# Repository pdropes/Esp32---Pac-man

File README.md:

# Esp32_ST7789_Pacman
 Remake of the famous pac-man, with some improvements

!!! NOTICE !!!

## Prepare
- This board was designed to be possible to do at home; the battery is the BL-5B or BL-5C, and the speaker is 32ohms from the 3310.
- In difficulty to find all components, the layout must be changed to support different ones.

## Development Environment
- [Arduino IDE](https://www.arduino.cc/en/main/software)
- [arduino-esp32](https://github.com/espressif/arduino-esp32)

1º Connect the board via USB to the PC.

2º The top buttons are for programming, on the left, IO0, on the right, RESET micro.
For the microcontroller to enter programming mode, the IO0 button must be held down while pressing the reset button briefly.

3º In the Arduino environment, choose "ESP32S2 Dev Module" board.

4º Upload, done.

## Controller
All commands are made on board by switches
LEFT-RIGHT-UP-DOWN , BUTTON A for new game, BUTTON B for pause

## Coding reference
- [Pacman-Arduino-Due](https://github.com/DrNCXCortex/Pacman-Arduino-Due)
- [esp32_ILI9328_Pacman](https://github.com/MhageGH/esp32_ILI9328_Pacman)

Changes:

- Schematic and connections for prototype
- ST7789 support
- Sounds trought two ESP32 8b DAC channels (ambient / effects)
- Functions of buttons A and B
- Show frightened ghosts blinking, before changing to normal
- Battery capacity monitor
- Hiscore saved in internal flash
- Slide-switch to select mode "off/charge" "on/mute" "on/sound"

Revision 1:
- "Battery" font, identical to the rest of the text
- In DEMO mode, the score always remains visible from the last game
- Added missing "Adafruit_BusIO" library

It was my first time programming in C, it may not be perfect.

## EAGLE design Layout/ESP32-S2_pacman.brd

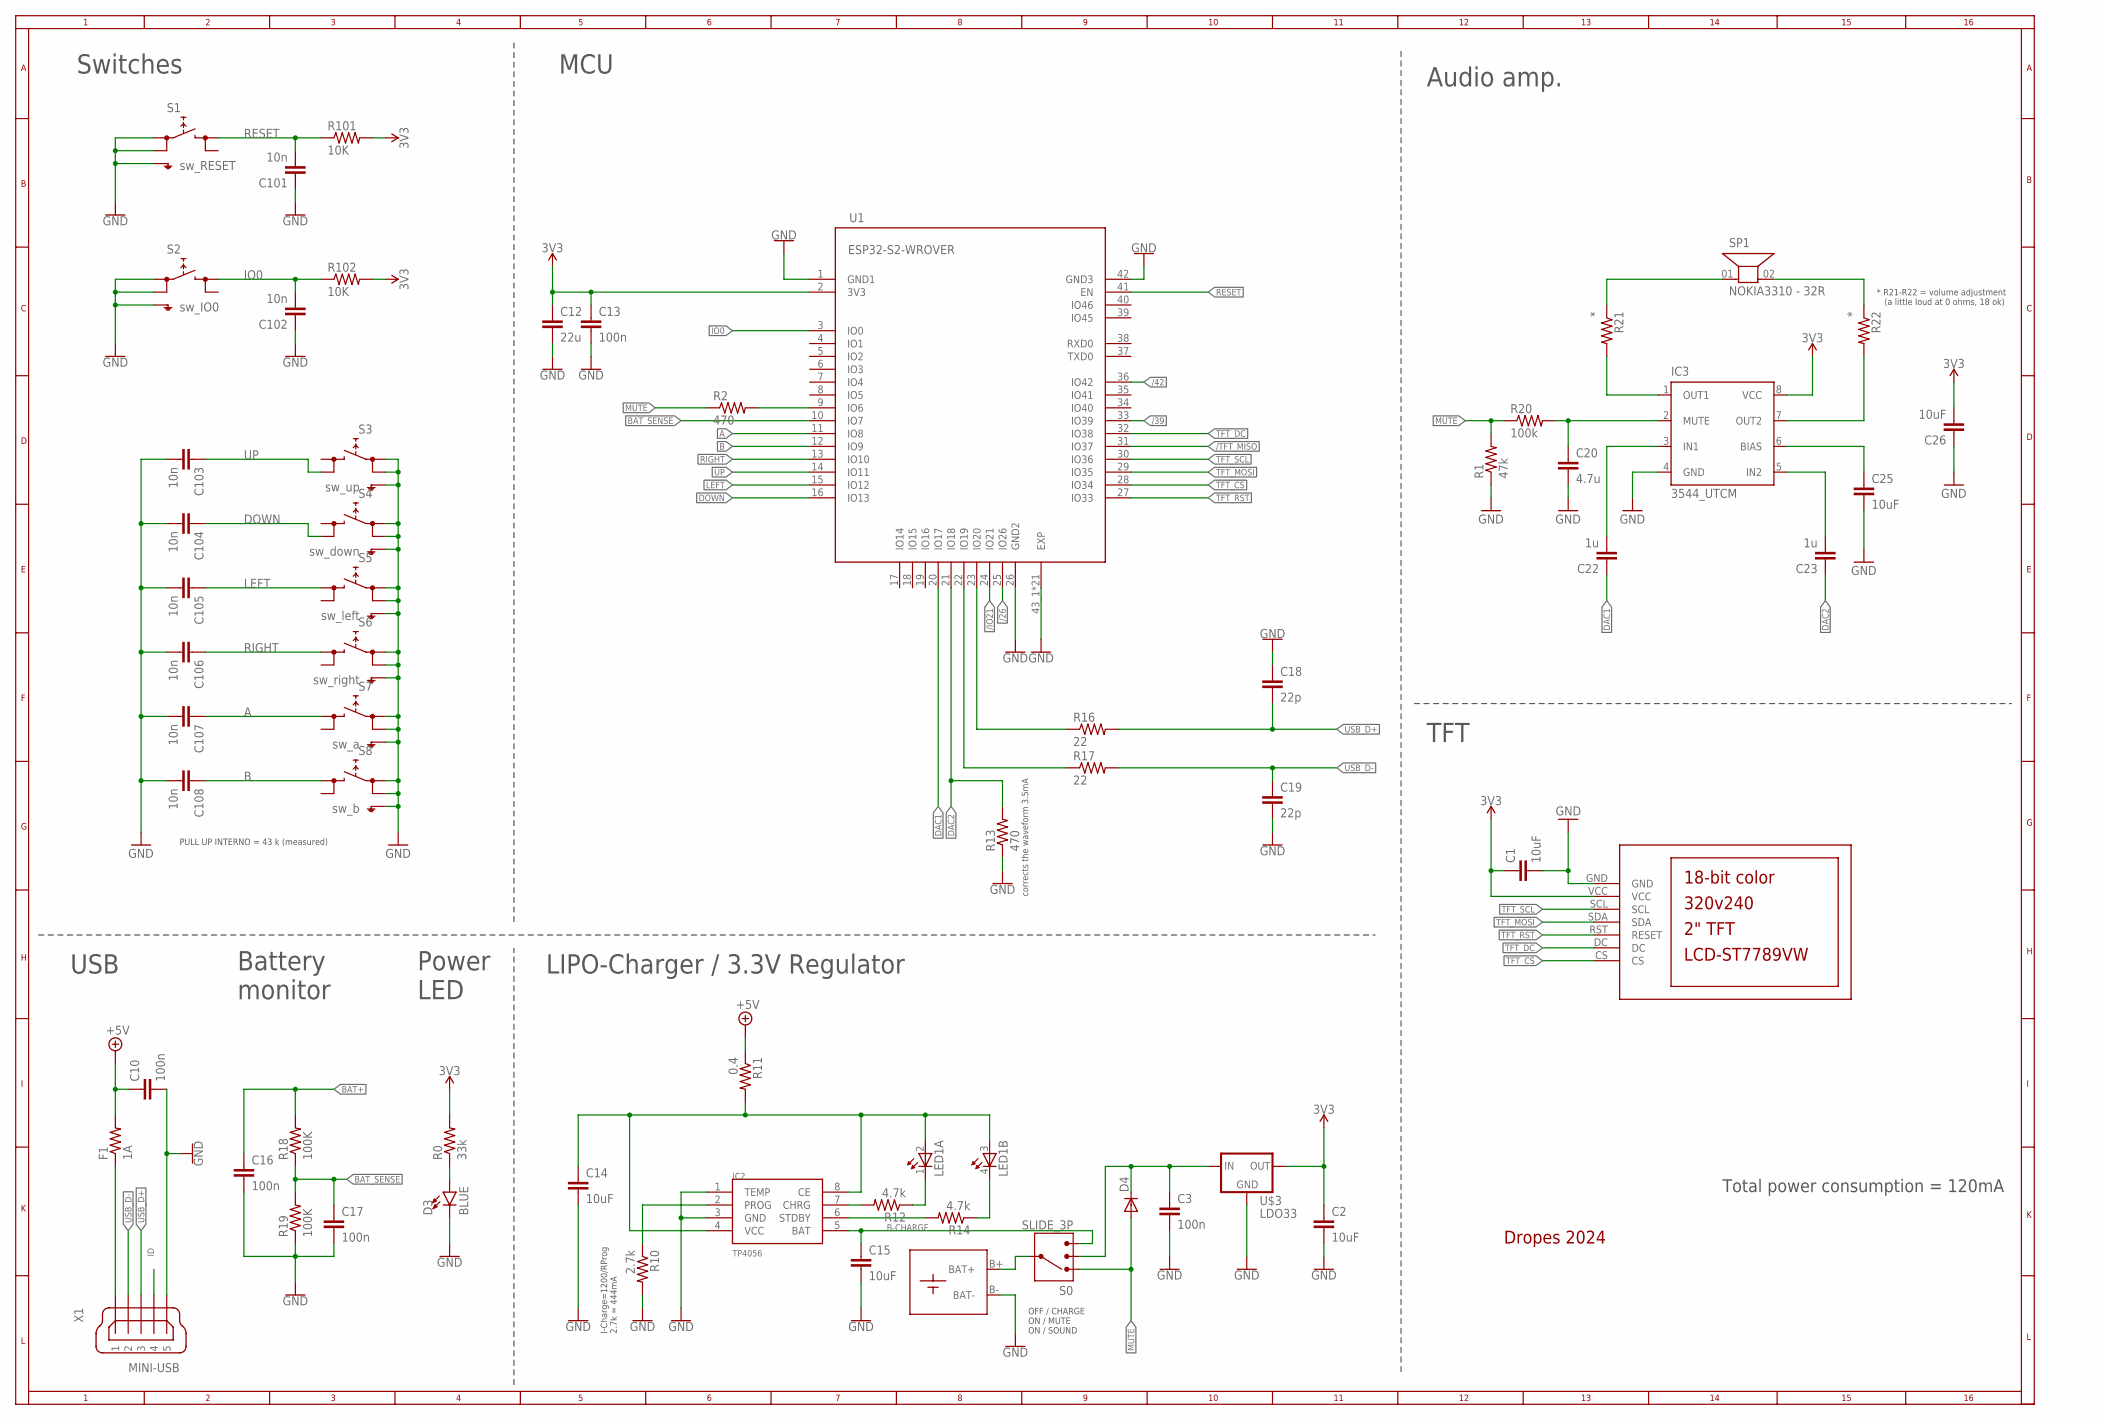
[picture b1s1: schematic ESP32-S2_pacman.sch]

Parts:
C1, C2, C14, C15: 10uF; 1206
C3, C10, C13, C16, C17: 100n; 0805
C12: 22u; 1206
C18, C19: 22p; 0805
C20: 4.7u; 0805
C22, C23: 1u; 0805
C25, C26: 10uF; 0805
C101, C102, C103, C104, C105, C106, C107, C108: 10n; 0805
D3: BLUE; LED-1206
D4: DIODE-SOD323-W; SOD323-W
F1: 1A; 0805
IC2: TP4056; SOP-8
IC3: 3544_UTCM; SO08
LED1: TOPLED-2--; P-LCC-4-2
R0: 33k; 0805
R1: 47k; 0805
R2, R13: 470; 0805
R10: 2.7k; 0805
R11: 0.4; 0805
R12, R14: 4.7k; 0805
R16, R17: 22; 0805
R18, R19: 100K; 0805
R20: 100k; 0805
R21, R22: *; 0805
R101, R102: 10K; 0805
S0: SLIDE_3P
S1: sw_RESET; SKHMPXE010
S2: sw_IO0; SKHMPXE010
S3: sw_up; SKHMPXE010
S4: sw_down; SKHMPXE010
S5: sw_left; SKHMPXE010
S6: sw_right; SKHMPXE010
S7: sw_a; SKHMPXE010
S8: sw_b; SKHMPXE010
SP1: NOKIA3310 - 32R; AL201P
U1: ESP32-S2-WROVER; MODULE_ESP32-S2-WROVER
U$1: NOKIA_LIPO; BATTERY
U$2: LCD-ST7789VW
U$3: LDO33; SOT89R
X1: MINI-USB; 32005-301

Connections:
+5V: C10.1, F1.2, R11.1
/26: U1.25 (IO26)
/39: U1.33 (IO39)
/42: U1.36 (IO42)
/IO21: U1.24 (IO21)
/TFT_MISO: U1.31 (IO37)
A: C107.1, S7.3 (2.1), U1.11 (IO8)
B: C108.1, S8.3 (2.1), U1.12 (IO9)
B-CHARGE: C15.1, IC2.5 (BAT), S0.P$4 (4)
BAT+: C16.1, R18.2, S0.P$1 (1), U$1.B+ (BAT+)
BAT++: C3.1, D4.C, S0.P$3 (3), U$3.2 (IN), U$3.'2 (IN)
BAT_SENSE: C17.1, R18.1, R19.2, U1.10 (IO7)
DAC1: C22.1, U1.20 (IO17)
DAC2: C23.1, R13.2, U1.21 (IO18)
DOWN: C104.1, S4.4 (2.2), U1.16 (IO13)
GND: C1.2, C2.2, C3.2, C10.2, C12.2, C13.2, C14.2, C15.2, C16.2, C17.2, C18.1, C19.2, C20.2, C25.2, C26.1, C101.1, C102.1, C103.2, C104.2, C105.2, C106.2, C107.2, C108.2, D3.C, IC2.1 (TEMP), IC2.3 (GND), IC3.4 (GND), R1.1, R10.2, R13.1, R19.1, S1.1 (1.1), S1.2 (1.2), S1.5 (SH), S2.1 (1.1), S2.2 (1.2), S2.5 (SH), S3.1 (1.1), S3.2 (1.2), S3.5 (SH), S4.1 (1.1), S4.2 (1.2), S4.5 (SH), S5.1 (1.1), S5.2 (1.2), S5.5 (SH), S6.1 (1.1), S6.2 (1.2), S6.5 (SH), S7.1 (1.1), S7.2 (1.2), S7.5 (SH), S8.1 (1.1), S8.2 (1.2), S8.5 (SH), U1.1 (GND1), U1.26 (GND2), U1.42 (GND3), U1.43_1 (EXP), U1.43_2 (EXP), U1.43_3 (EXP), U1.43_4 (EXP), U1.43_5 (EXP), U1.43_6 (EXP), U1.43_7 (EXP), U1.43_8 (EXP), U1.43_9 (EXP), U1.43_10 (EXP), U1.43_11 (EXP), U1.43_12 (EXP), U1.43_13 (EXP), U1.43_14 (EXP), U1.43_15 (EXP), U1.43_16 (EXP), U1.43_17 (EXP), U1.43_18 (EXP), U1.43_19 (EXP), U1.43_20 (EXP), U1.43_21 (EXP), U$1.B- (BAT-), U$2.GND, U$3.1 (GND), X1.5
ID: X1.4
IN1: C22.2, IC3.3 (IN1)
IO0: C102.2, R102.1, S2.3 (2.1), U1.3 (IO0)
IO52: R16.1, U1.23 (IO20)
IO53: R17.1, U1.22 (IO19)
LEFT: C105.1, S5.3 (2.1), U1.15 (IO12)
MUTE: D4.A, R1.2, R2.1, R20.1, S0.P$2 (2)
unnamed: R21.1, SP1.01 (1)
unnamed: D3.A, R0.1
unnamed: C20.1, IC3.2 (MUTE), R20.2
unnamed: R2.2, U1.9 (IO6)
unnamed: R22.1, SP1.02 (2)
unnamed: IC3.1 (OUT1), R21.2
unnamed: C25.1, IC3.6 (BIAS)
unnamed: IC3.7 (OUT2), R22.2
unnamed: C23.2, IC3.5 (IN2)
unnamed: IC2.2 (PROG), R10.1
unnamed: IC2.7 (CHRG), R12.2
unnamed: IC2.6 (STDBY), R14.2
unnamed: LED1.1 (C), R12.1
unnamed: LED1.4 (C), R14.1
unnamed: C14.1, IC2.4 (VCC), IC2.8 (CE), LED1.2 (A), LED1.3 (A), R11.2
RESET: C101.2, R101.1, S1.3 (2.1), U1.41 (EN)
RIGHT: C106.1, S6.3 (2.1), U1.13 (IO10)
TFT_CS: U1.28 (IO34), U$2.CS
TFT_DC: U1.32 (IO38), U$2.DC
TFT_MOSI: U1.29 (IO35), U$2.SDA
TFT_RST: U1.27 (IO33), U$2.RST (RESET)
TFT_SCL: U1.30 (IO36), U$2.SCL
UP: C103.1, S3.4 (2.2), U1.14 (IO11)
USB+: F1.1, X1.1
USB_D+: C18.2, R16.2, X1.3
USB_D-: C19.1, R17.2, X1.2
VCC: C1.1, C2.1, C12.1, C13.1, C26.2, IC3.8 (VCC), R0.2, R101.2, R102.2, U1.2 (3V3), U$2.VCC, U$3.3 (OUT)

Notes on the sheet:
MCU
USB
TFT
Switches
Audio amp.
corrects the waveform 3.5mA
Total power consumption = 120mA
LIPO-Charger / 3.3V Regulator
I-Charge=1200/RProg 2.7k = 444mA
OFF / CHARGE ON / MUTE ON / SOUND
PULL UP INTERNO = 43 k (measured)
Battery monitor
Power LED
* R21-R22 = volume adjustment (a little loud at 0 ohms, 18 ok)
Dropes 2024

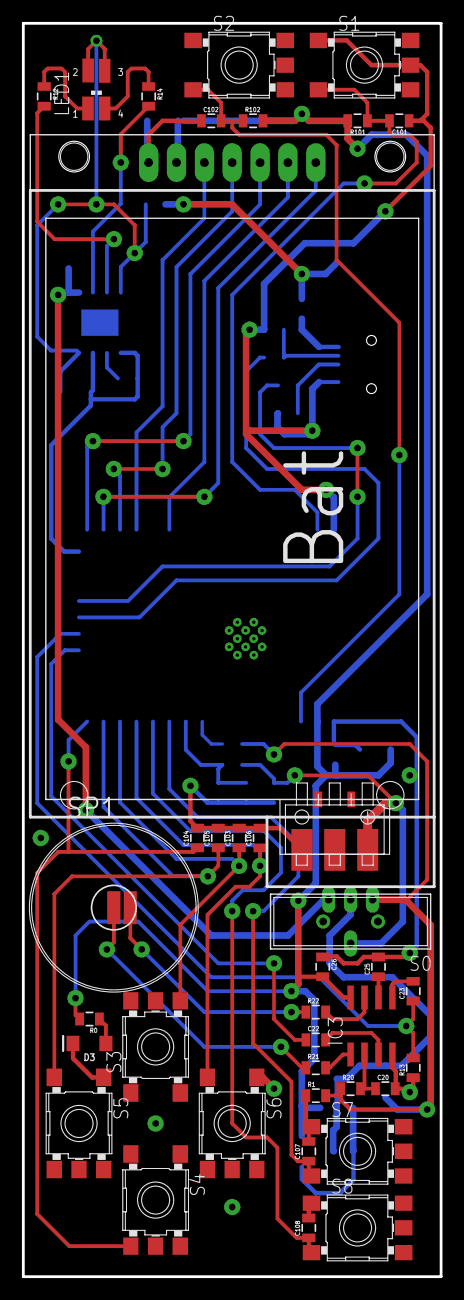
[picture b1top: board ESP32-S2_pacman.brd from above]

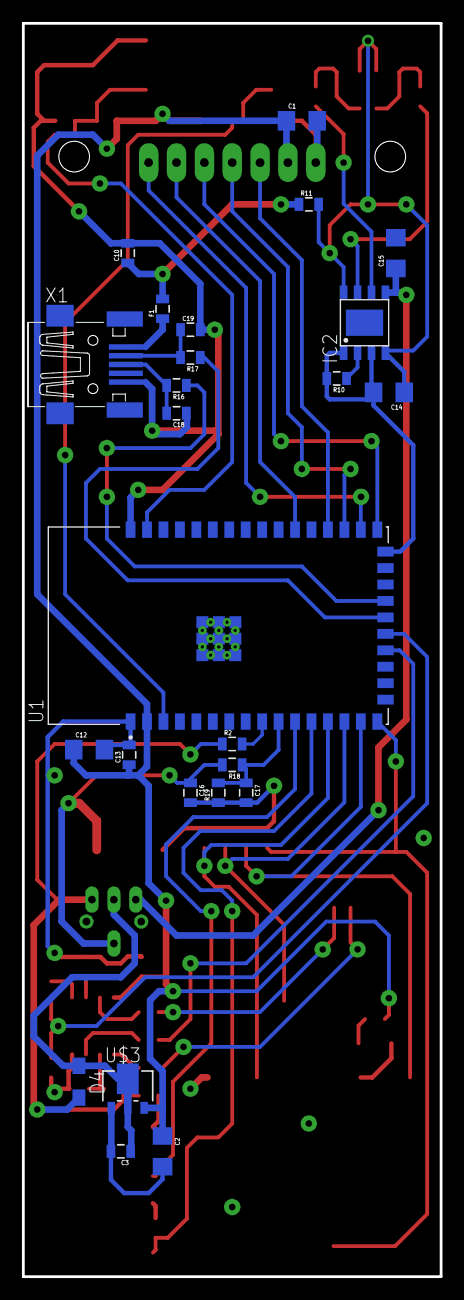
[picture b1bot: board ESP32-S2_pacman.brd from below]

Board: 2 copper layers, 38.1 x 114.3 mm, 63 parts (25 on the bottom side), 44 nets.

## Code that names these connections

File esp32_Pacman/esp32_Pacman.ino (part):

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
//LCD_ST7789 :
/*
#define TFT_MOSI 35 
#define TFT_SCLK 36 
*/
#define TFT_CS   34 
#define TFT_DC   38
#define TFT_RST  33
Adafruit_ST7789 tft = Adafruit_ST7789(TFT_CS, TFT_DC, TFT_RST);


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

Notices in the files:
esp32_Pacman/esp32_Pacman.ino:
Copyright (c) 2014  Dr. NCX (mirracle.mxx@gmail.com)
MIT license, all text above must be included in any redistribution.
parts and their libraries:
SparkFun: Licensing: CC v3.0 Share-Alike You are welcome to use this library for commercial purposes.
SparkFun-LED: Licensing: Creative Commons ShareAlike 4.0 International - https://creativecommons.org/licenses/by-sa/4.0
